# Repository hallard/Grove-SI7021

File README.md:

Grove SI7021 Temperature and Humidity Sensor
============================================

Boards made for testing and validate Ultra Low Power node boards you can connect grove connector to make it original "grove" or header pin to make it for breadboarding.

- The SI7021 pads have been resized to be easily hand soldered with an iron soldering.
- You can enable/disable the pullup with a solder pad.
- This board as no regulator on board, should be used only with 3.3V devices or add a level shifter.

##Detailed Description

Everything about ULPNode used with this board is located [here][1] on my blog

##Schematics

##Boards  
&nbsp;
&nbsp;

You can order PCB directly from [OSHPark](https://oshpark.com/shared_projects/upb8JwuB)

##Library
There are lot of library to drive this one, the Sparkfun's [one][3] works fine

##Picture of assembled boards

##Misc
See news and other projects on my [blog][2] 
 
[1]: https://hallard.me/category/ulpnode/
[2]: http://hallard.me
[3]: https://github.com/sparkfun/SparkFun_HTU21D_Breakout_Arduino_Library

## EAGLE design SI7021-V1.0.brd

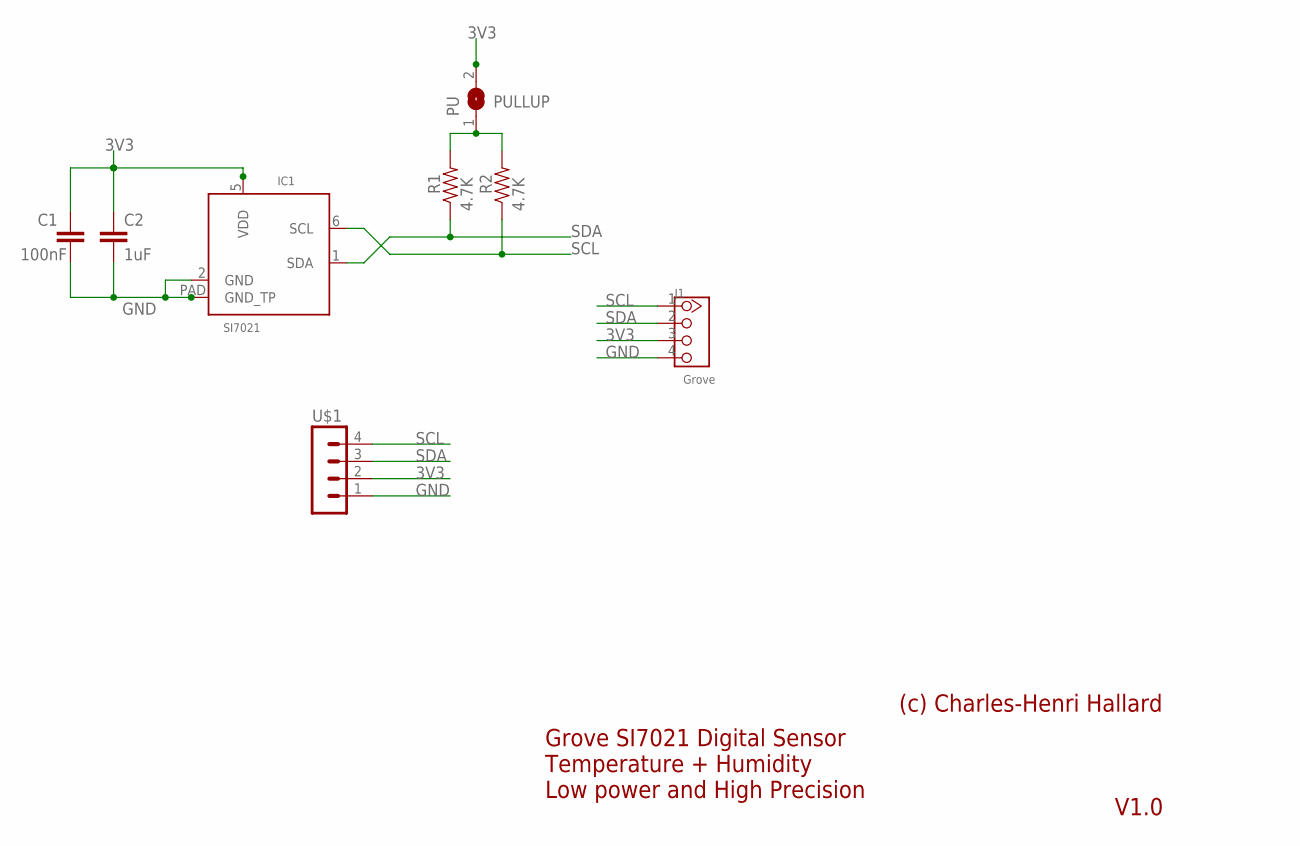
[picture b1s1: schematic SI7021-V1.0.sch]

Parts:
C1: 100nF; 0805-CAP
C2: 1uF; 0805-CAP
IC1: SI7021; DFN6-3X3-LONG
J1: Grove; 4P-2.0
PU: SOLDERJUMPERREFLOW_NOPASTE; SOLDERJUMPER_REFLOW_NOPASTE
R1, R2: 4.7K; 0805-RES
U$1: CON_HEADER_1X04'SMALL''; M1X4

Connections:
3V3: C1.1, C2.1, IC1.5 (VDD), J1.3, PU.2, U$1.2
GND: C1.2, C2.2, IC1.2 (GND), IC1.PAD (GND_TP), J1.4, U$1.1
PULLUP: PU.1, R1.2, R2.2
SCL: IC1.6 (SCL), J1.1, R2.1, U$1.4
SDA: IC1.1 (SDA), J1.2, R1.1, U$1.3

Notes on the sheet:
Grove SI7021 Digital Sensor Temperature + Humidity Low power and High Precision
(c) Charles-Henri Hallard
V1.0

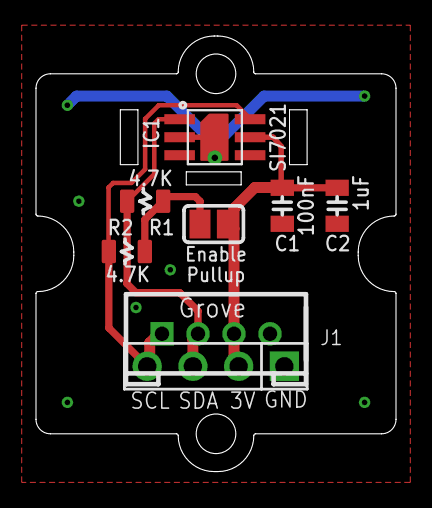
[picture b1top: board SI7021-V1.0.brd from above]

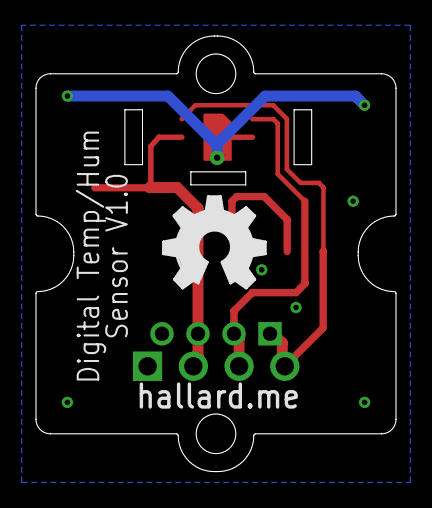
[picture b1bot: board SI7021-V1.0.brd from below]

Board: 2 copper layers, 20.0 x 24.2 mm, 10 parts (2 on the bottom side), 5 nets.

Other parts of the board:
U$2: 1U-DIM-W/-DRILL
U$4: OSHW_FILLX200_NOTEXT

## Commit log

2015-07-20 :space_invader: Added .gitattributes & .gitignore files
2015-07-20 Creation
2015-07-20 Link Error
2015-07-20 Addes OSKPArk link
2015-07-20 Added more description
2015-07-20 Added note on 3.3V power

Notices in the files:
parts and their libraries:
microbuilder: This work is placed in the public domain, and may be freely used for commercial and non-commercial work with the following conditions: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
